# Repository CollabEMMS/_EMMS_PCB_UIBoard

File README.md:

# _EMMS_PCB_UserInterface-Board
Physical User Interface PCB Files
<p>Confirmed Latest Version as 2/6/2020

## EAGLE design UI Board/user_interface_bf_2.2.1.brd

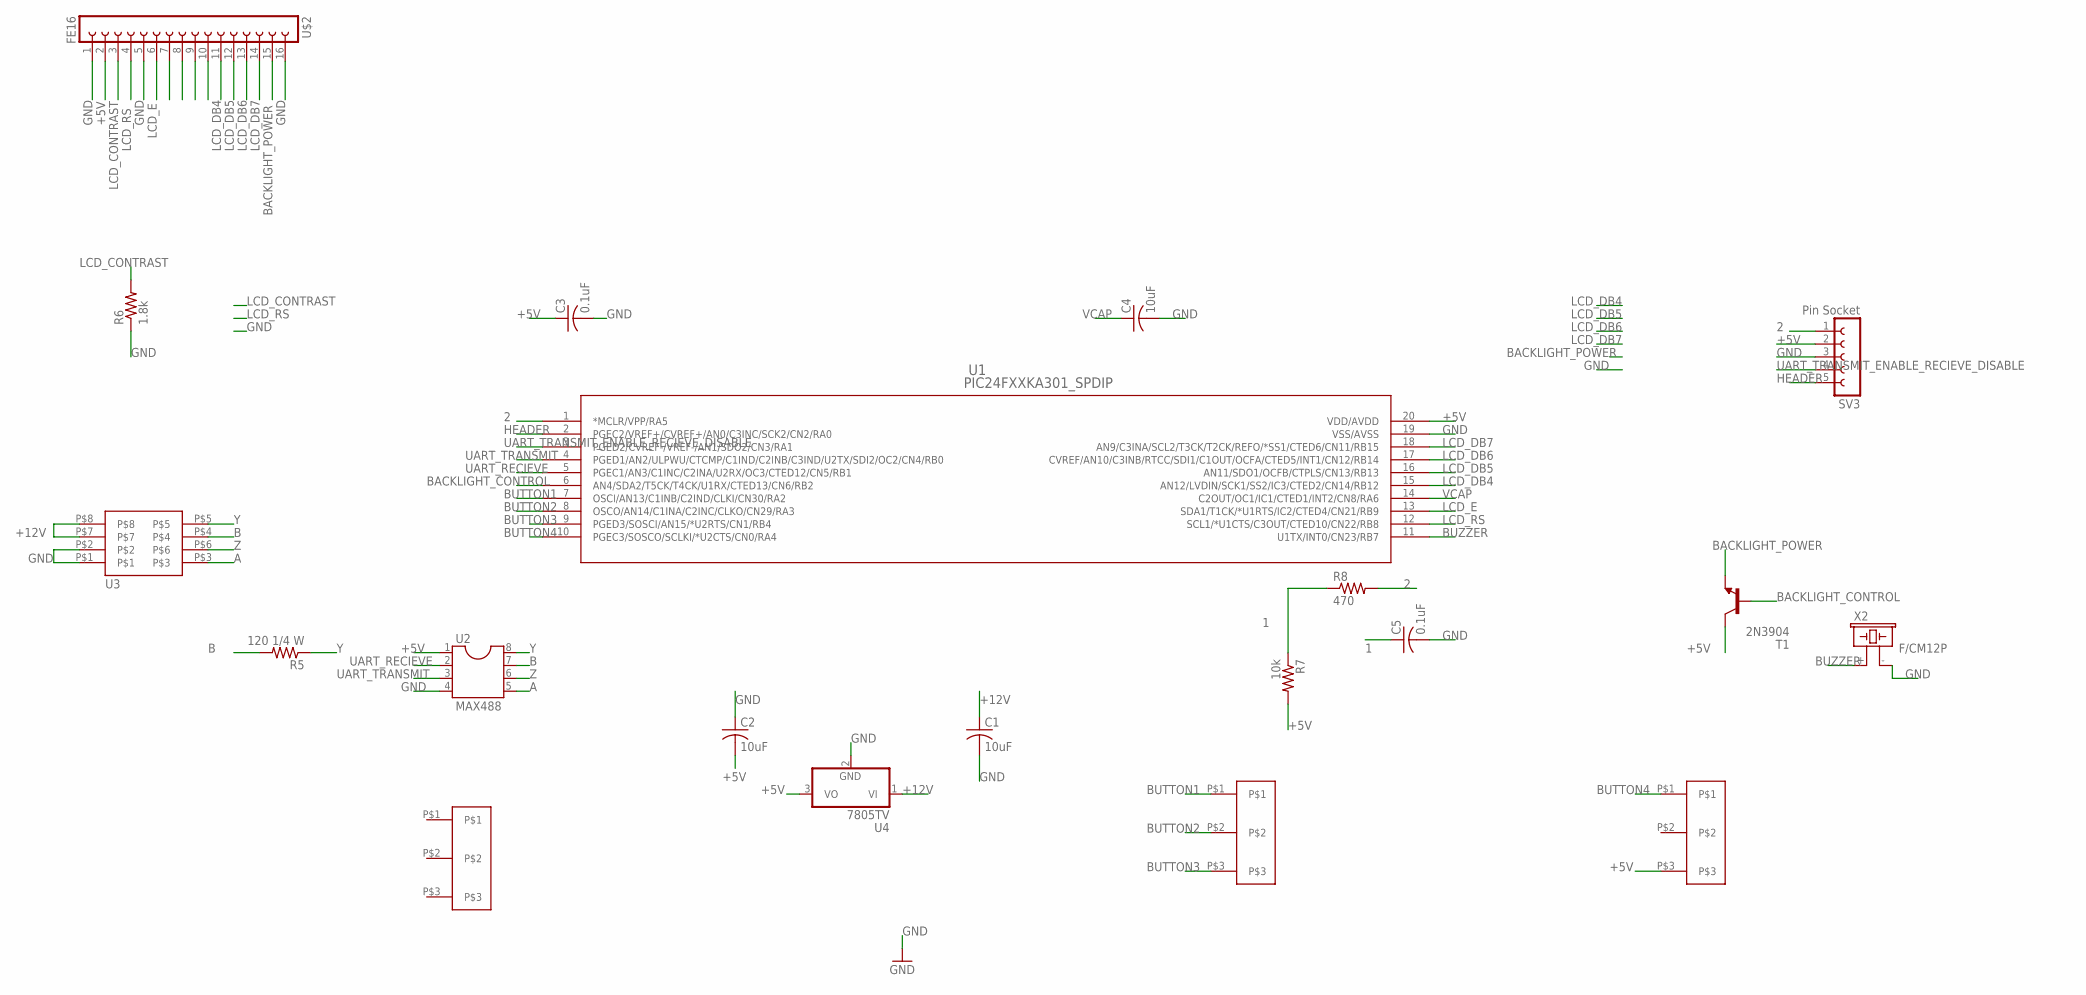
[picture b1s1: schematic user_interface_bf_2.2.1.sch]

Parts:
C1, C2, C4: 10uF; C050-025X075
C3, C5: 0.1uF; C050-025X075
R5: 120 1/4 W; 0207/10
R6: 1.8k; 0207/10
R7: 10k; 0207/10
R8: 470; 0207/10
SV3: Pin Socket; FE05-1
T1: 2N3904; TO92
U1: PIC24FXXKA301_SPDIP; SPDIP20_300MC
U2: MAX488; DIL08
U3: CAT5
U4: 7805TV; TO220V
U6, U7: 3_PIN_FEMALE_HEADER
U$2: FE16
U$4: 3_PIN_FEMALE_HEADER
X2: F/CM12P

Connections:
1: C5.1, R7.1, R8.1
2: R8.2, SV3.1, U1.1 (*MCLR/VPP/RA5)
+5V: C2.2, C3.1, R7.2, SV3.2, T1.1 (C), U1.20 (VDD/AVDD), U2.1, U4.3 (VO), U7.P$3, U$2.2
+12V: C1.1, U3.P$7, U3.P$8, U4.1 (VI)
A: U2.5, U3.P$3
B: R5.2, U2.7, U3.P$4
BACKLIGHT_CONTROL: T1.2 (B), U1.6 (AN4/SDA2/T5CK/T4CK/U1RX/CTED13/CN6/RB2)
BACKLIGHT_POWER: T1.3 (E), U$2.15
BUTTON1: U1.7 (OSCI/AN13/C1INB/C2IND/CLKI/CN30/RA2), U6.P$1
BUTTON2: U1.8 (OSCO/AN14/C1INA/C2INC/CLKO/CN29/RA3), U6.P$2
BUTTON3: U1.9 (PGED3/SOSCI/AN15/*U2RTS/CN1/RB4), U6.P$3
BUTTON4: U1.10 (PGEC3/SOSCO/SCLKI/*U2CTS/CN0/RA4), U7.P$1
BUZZER: U1.11 (U1TX/INT0/CN23/RB7), X2.+ (1)
GND: C1.2, C2.1, C3.2, C4.2, C5.2, R6.1, SV3.3, U1.19 (VSS/AVSS), U2.4, U3.P$1, U3.P$2, U4.2 (GND), U$2.1, U$2.5, U$2.16, X2.- (2)
HEADER: SV3.5, U1.2 (PGEC2/VREF+/CVREF+/AN0/C3INC/SCK2/CN2/R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)
LCD_CONTRAST: R6.2, U$2.3
LCD_DB4: U1.15 (AN12/LVDIN/SCK1/SS2/IC3/CTED2/CN14/RB12), U$2.11
LCD_DB5: U1.16 (AN11/SDO1/OCFB/CTPLS/CN13/RB13), U$2.12
LCD_DB6: U1.17 (CVREF/AN10/C3INB/RTCC/SDI1/C1OUT/OCFA/C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), U$2.13
LCD_DB7: U1.18 (AN9/C3INA/SCL2/T3CK/T2CK/REFO/*SS1/CTED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), U$2.14
LCD_E: U1.13 (SDA1/T1CK/*U1RTS/IC2/CTED4/CN21/RB9), U$2.6
LCD_RS: U1.12 (SCL1/*U1CTS/C3OUT/CTED10/CN22/RB8), U$2.4
UART_RECIEVE: U1.5 (PGEC1/AN3/C1INC/C2INA/U2RX/OC3/CTED12/C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), U2.2
UART_TRANSMIT: U1.4 (PGED1/AN2/ULPWU/CTCMP/C1IND/C2INB/C3IND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), U2.3
UART_TRANSMIT_ENABLE_RECIEVE_DISABLE: SV3.4, U1.3 (PGED2/CVREF-/VREF-/AN1/SDO2/CN3/RA1)
VCAP: C4.1, U1.14 (C2OUT/OC1/IC1/CTED1/INT2/CN8/RA6)
Y: R5.1, U2.8, U3.P$5
Z: U2.6, U3.P$6

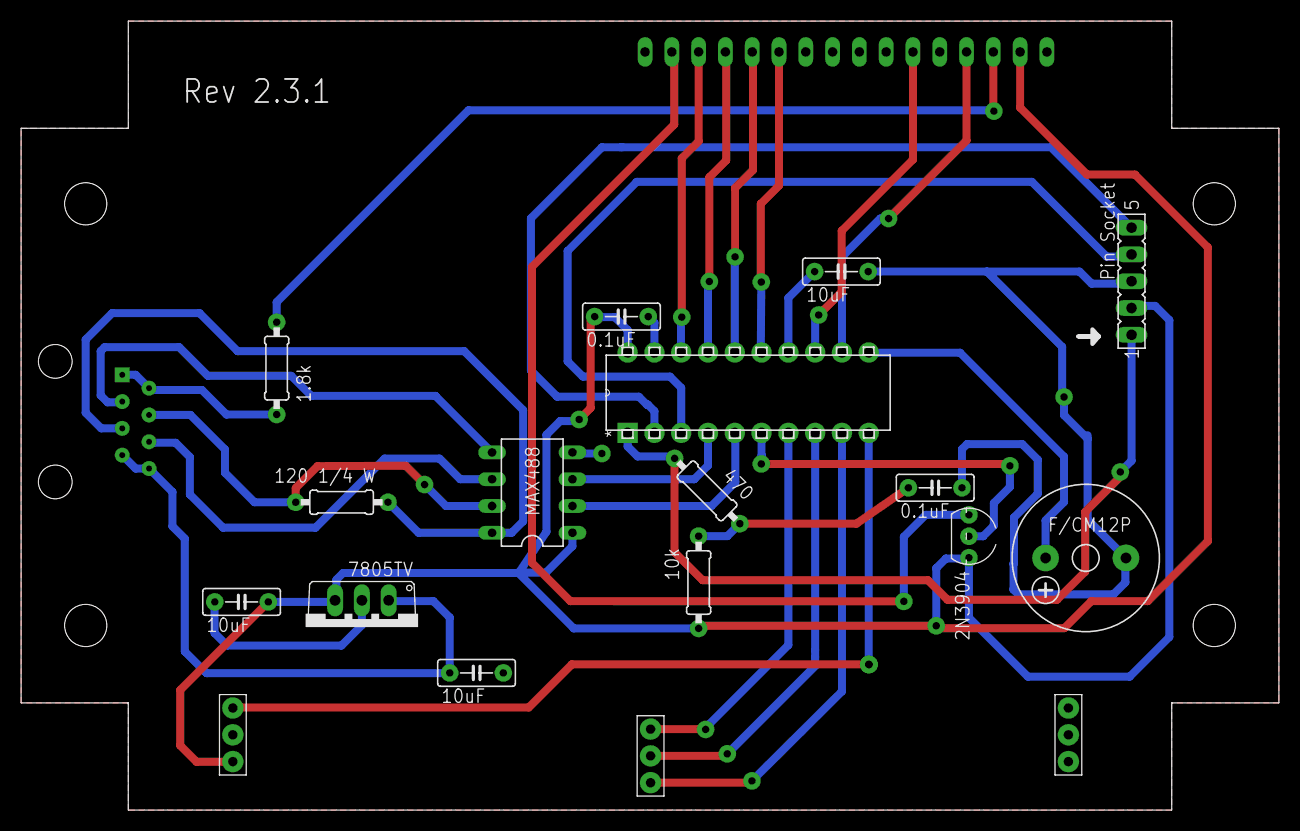
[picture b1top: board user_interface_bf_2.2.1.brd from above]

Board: 2 copper layers, 119.3 x 74.8 mm, 20 parts (1 on the bottom side), 28 nets.

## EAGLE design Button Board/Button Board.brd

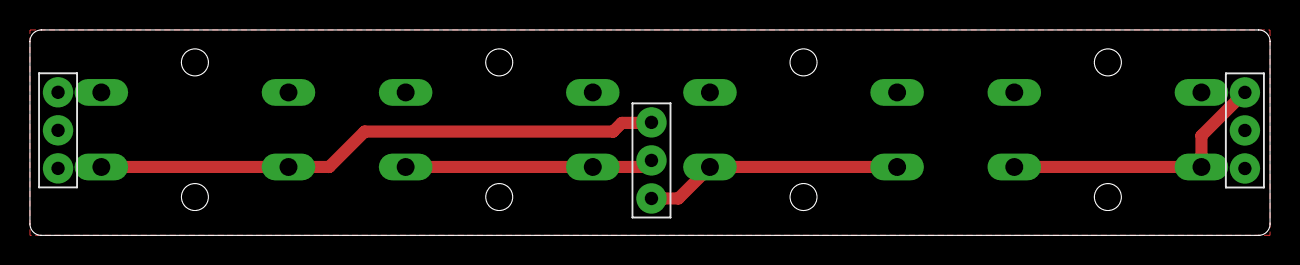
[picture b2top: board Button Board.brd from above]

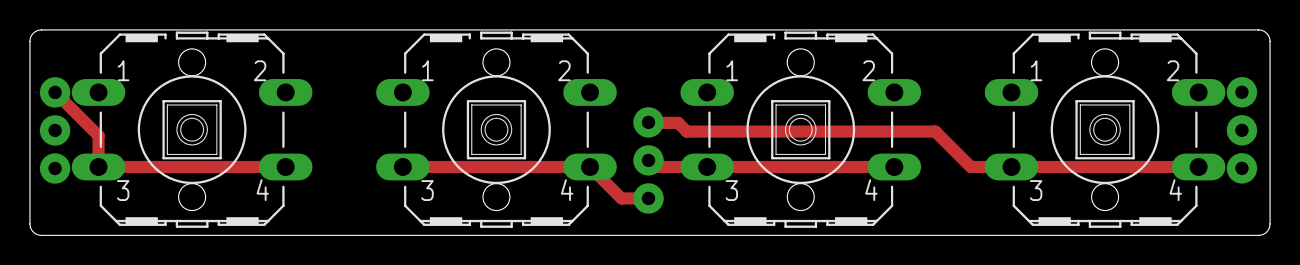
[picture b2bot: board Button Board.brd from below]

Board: 2 copper layers, 82.8 x 13.7 mm, 7 parts (4 on the bottom side), 5 nets.

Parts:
S1, S2, S3, S4: B3F-40XX
U$1, U$2, U$3: 3_PIN_FEMALE_HEADER

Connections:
unnamed: S1.3, S1.4, U$2.P$1
unnamed: S2.3, S2.4, U$2.P$2
unnamed: S3.3, S3.4, U$2.P$3
unnamed: S4.3, S4.4, U$3.P$1
VCC: S1.1, S1.2, S2.1, S2.2, S3.1, S3.2, S4.1, S4.2, U$3.P$3

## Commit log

2018-02-08 Init Files
2018-02-08 Chaned right fastening holes
    Right Holes were out of place. Moved right holes .5mm to the left. Rerouted a trace to accomadate the move. Enlarged the diameter of all fastening holes to 4mm.
2018-02-13 Added LCD standoff screw holes
    Screw holes for the LCD standoffs on the bottom holes of the LCD were added w/ a diameter of 4mm. A few traces were moved to account for the added holes
2018-02-20 Updated CL
2019-02-21 2.3.1
    Updated version number
    Updated Screw Positions
    Fixed Missing Trace
2019-03-05 UI board PCB Fix
2019-03-12 Button Board with added holes
2019-03-12 add buttons holes
2019-03-14 Revert "add buttons holes"
    This reverts commit ba565238787d3dd891b7ae4447ef91bf21c13f6a.
2019-03-14 Revert "Revert "add buttons holes""
    This reverts commit 420c8f070e3c07ee863b894c9b89e1ea1063e732.
2019-03-14 Revert "Revert "Revert "add buttons holes"""
    This reverts commit e19daee898482ed2ce374b21b4aa321d85db5d35.
2019-03-14 Final Button Board Edits
    Edited dimension and VCC plane
2019-03-15 Gerbers
2020-02-06 Removed Button Board folder
    Contents were removed to the PCB_ButtonBoard Repository, so they were no longer needed in this repository
